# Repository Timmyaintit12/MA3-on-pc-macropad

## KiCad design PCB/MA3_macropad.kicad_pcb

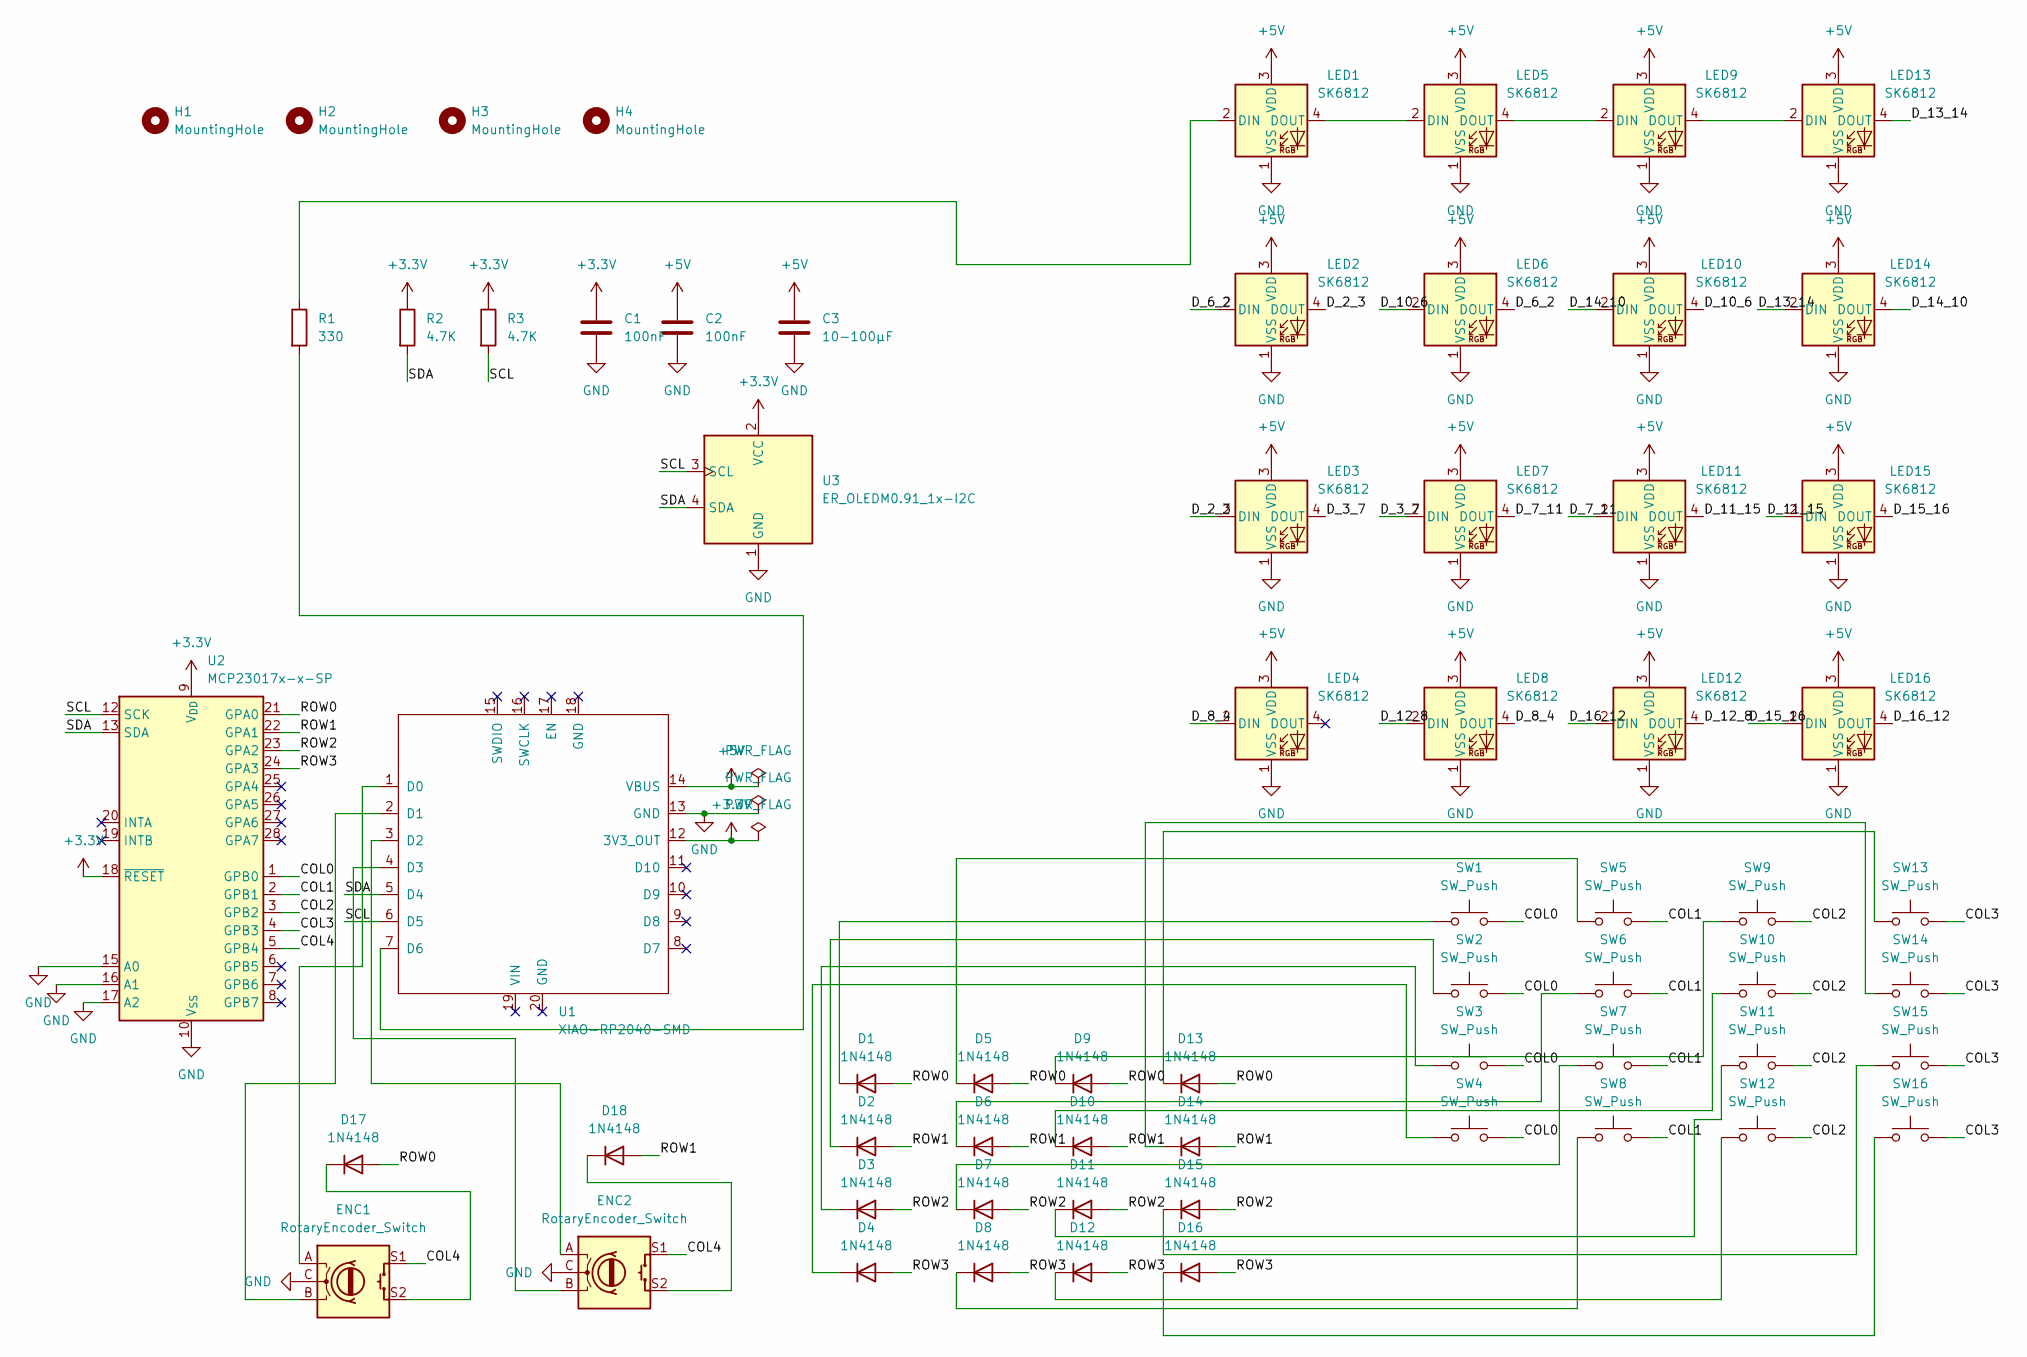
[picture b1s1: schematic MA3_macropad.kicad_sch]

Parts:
C1, C2: 100nF; C_Disc_D5.0mm_W2.5mm_P5.00mm
C3: 10-100µF; CP_Radial_D5.0mm_P2.00mm
D1, D2, D3, D4, D5, D6, D7, D8, D9, D10, D11, D12, D13, D14, D15, D16, D17, D18: 1N4148; D_DO-35_SOD27_P7.62mm_Horizontal
ENC1, ENC2: RotaryEncoder_Switch; RotaryEncoder_Alps_EC11E-Switch_Vertical_H20mm
H1, H2, H3, H4: MountingHole; MountingHole_3.2mm_M3
LED1, LED2, LED3, LED4, LED5, LED6, LED7, LED8, LED9, LED10, LED11, LED12, LED13, LED14, LED15, LED16: SK6812; LED_SK6812_PLCC4_5.0x5.0mm_P3.2mm
R1: 330; R_Axial_DIN0207_L6.3mm_D2.5mm_P7.62mm_Horizontal
R2, R3: 4.7K; R_Axial_DIN0207_L6.3mm_D2.5mm_P7.62mm_Horizontal
SW1, SW2, SW3, SW4, SW5, SW6, SW7, SW8, SW9, SW10, SW11, SW12, SW13, SW14, SW15, SW16: SW_Push; SW_Cherry_MX_1.00u_PCB
U1: XIAO-RP2040-SMD; XIAO-RP2040-DIP
U2: MCP23017x-x-SP; DIP-28_W7.62mm
U3: ER_OLEDM0.91_1x-I2C; PinSocket_1x04_P2.54mm_Vertical

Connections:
+3.3V: C1.1, R2.1, R3.1, U1.12 (3V3_OUT), U2.9 (V_{DD}), U2.18 (~RESET), U3.2 (VCC)
+5V: C2.1, C3.1, LED1.3 (VDD), LED2.3 (VDD), LED3.3 (VDD), LED4.3 (VDD), LED5.3 (VDD), LED6.3 (VDD), LED7.3 (VDD), LED8.3 (VDD), LED9.3 (VDD), LED10.3 (VDD), LED11.3 (VDD), LED12.3 (VDD), LED13.3 (VDD), LED14.3 (VDD), LED15.3 (VDD), LED16.3 (VDD), U1.14 (VBUS)
/COL0: SW1.2, SW2.2, SW3.2, SW4.2, U2.1 (GPB0)
/COL1: SW5.2, SW6.2, SW7.2, SW8.2, U2.2 (GPB1)
/COL2: SW9.2, SW10.2, SW11.2, SW12.2, U2.3 (GPB2)
/COL3: SW13.2, SW14.2, SW15.2, SW16.2, U2.4 (GPB3)
/COL4: ENC1.S1, ENC2.S1, U2.5 (GPB4)
/D_2_3: LED2.4 (DOUT), LED3.2 (DIN)
/D_3_7: LED3.4 (DOUT), LED7.2 (DIN)
/D_6_2: LED2.2 (DIN), LED6.4 (DOUT)
/D_7_11: LED7.4 (DOUT), LED11.2 (DIN)
/D_8_4: LED4.2 (DIN), LED8.4 (DOUT)
/D_10_6: LED6.2 (DIN), LED10.4 (DOUT)
/D_11_15: LED11.4 (DOUT), LED15.2 (DIN)
/D_12_8: LED8.2 (DIN), LED12.4 (DOUT)
/D_13_14: LED13.4 (DOUT), LED14.2 (DIN)
/D_14_10: LED10.2 (DIN), LED14.4 (DOUT)
/D_15_16: LED15.4 (DOUT), LED16.2 (DIN)
/D_16_12: LED12.2 (DIN), LED16.4 (DOUT)
/ROW0: D1.2 (A), D5.2 (A), D9.2 (A), D13.2 (A), D17.2 (A), U2.21 (GPA0)
/ROW1: D2.2 (A), D6.2 (A), D10.2 (A), D14.2 (A), D18.2 (A), U2.22 (GPA1)
/ROW2: D3.2 (A), D7.2 (A), D11.2 (A), D15.2 (A), U2.23 (GPA2)
/ROW3: D4.2 (A), D8.2 (A), D12.2 (A), D16.2 (A), U2.24 (GPA3)
/SCL: R3.2, U1.6 (D5), U2.12 (SCK), U3.3 (SCL)
/SDA: R2.2, U1.5 (D4), U2.13 (SDA), U3.4 (SDA)
GND: C1.2, C2.2, C3.2, ENC1.C, ENC2.C, LED1.1 (VSS), LED2.1 (VSS), LED3.1 (VSS), LED4.1 (VSS), LED5.1 (VSS), LED6.1 (VSS), LED7.1 (VSS), LED8.1 (VSS), LED9.1 (VSS), LED10.1 (VSS), LED11.1 (VSS), LED12.1 (VSS), LED13.1 (VSS), LED14.1 (VSS), LED15.1 (VSS), LED16.1 (VSS), U1.13 (GND), U2.10 (V_{SS}), U2.15 (A0), U2.16 (A1), U2.17 (A2), U3.1 (GND)
unnamed: D1.1 (K), SW1.1
unnamed: D2.1 (K), SW2.1
unnamed: D3.1 (K), SW3.1
unnamed: D4.1 (K), SW4.1
unnamed: D5.1 (K), SW5.1
unnamed: D6.1 (K), SW6.1
unnamed: D7.1 (K), SW7.1
unnamed: D8.1 (K), SW8.1
unnamed: D9.1 (K), SW9.1
unnamed: D10.1 (K), SW10.1
unnamed: D11.1 (K), SW11.1
unnamed: D12.1 (K), SW12.1
unnamed: D13.1 (K), SW13.1
unnamed: D14.1 (K), SW14.1
unnamed: D15.1 (K), SW15.1
unnamed: D16.1 (K), SW16.1
unnamed: D17.1 (K), ENC1.S2
unnamed: D18.1 (K), ENC2.S2
unnamed: LED1.2 (DIN), R1.1
unnamed: LED1.4 (DOUT), LED5.2 (DIN)
unnamed: LED5.4 (DOUT), LED9.2 (DIN)
unnamed: LED9.4 (DOUT), LED13.2 (DIN)
unnamed: ENC1.A, U1.1 (D0)
unnamed: ENC1.B, U1.2 (D1)
unnamed: ENC2.A, U1.3 (D2)
unnamed: ENC2.B, U1.4 (D3)
unnamed: R1.2, U1.7 (D6)

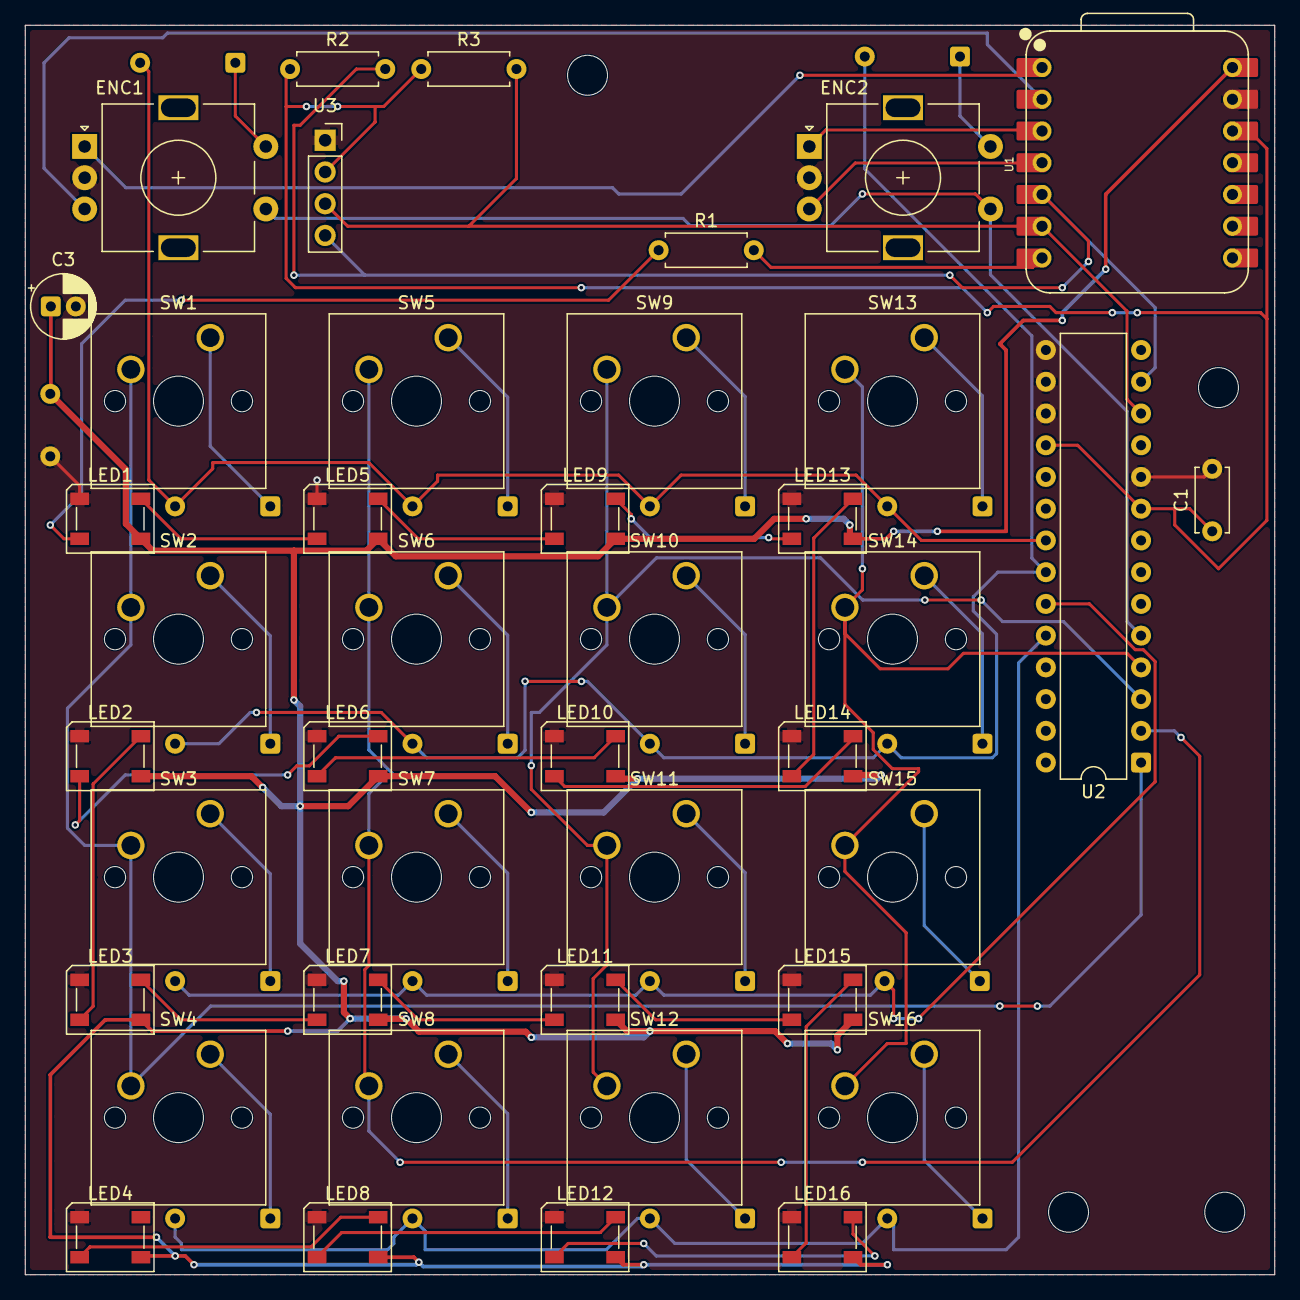
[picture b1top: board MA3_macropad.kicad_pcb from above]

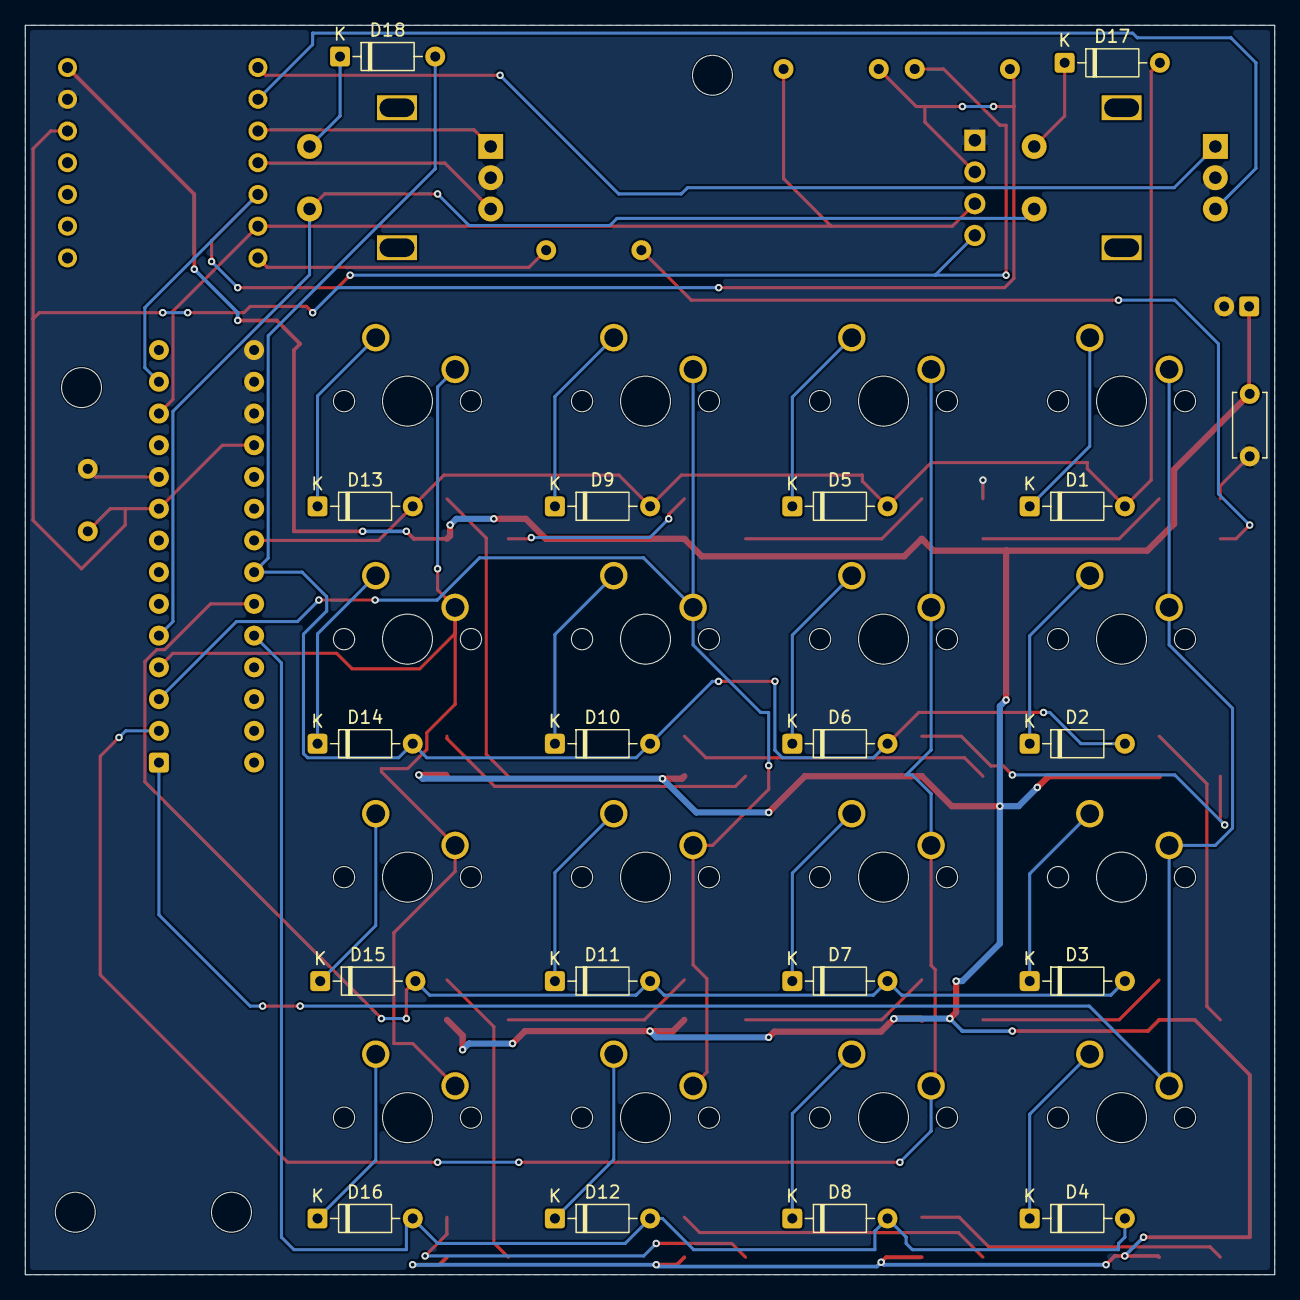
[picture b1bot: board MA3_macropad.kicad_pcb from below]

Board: 2 copper layers, 100.0 x 100.0 mm, 65 parts (19 on the bottom side), 53 nets.
